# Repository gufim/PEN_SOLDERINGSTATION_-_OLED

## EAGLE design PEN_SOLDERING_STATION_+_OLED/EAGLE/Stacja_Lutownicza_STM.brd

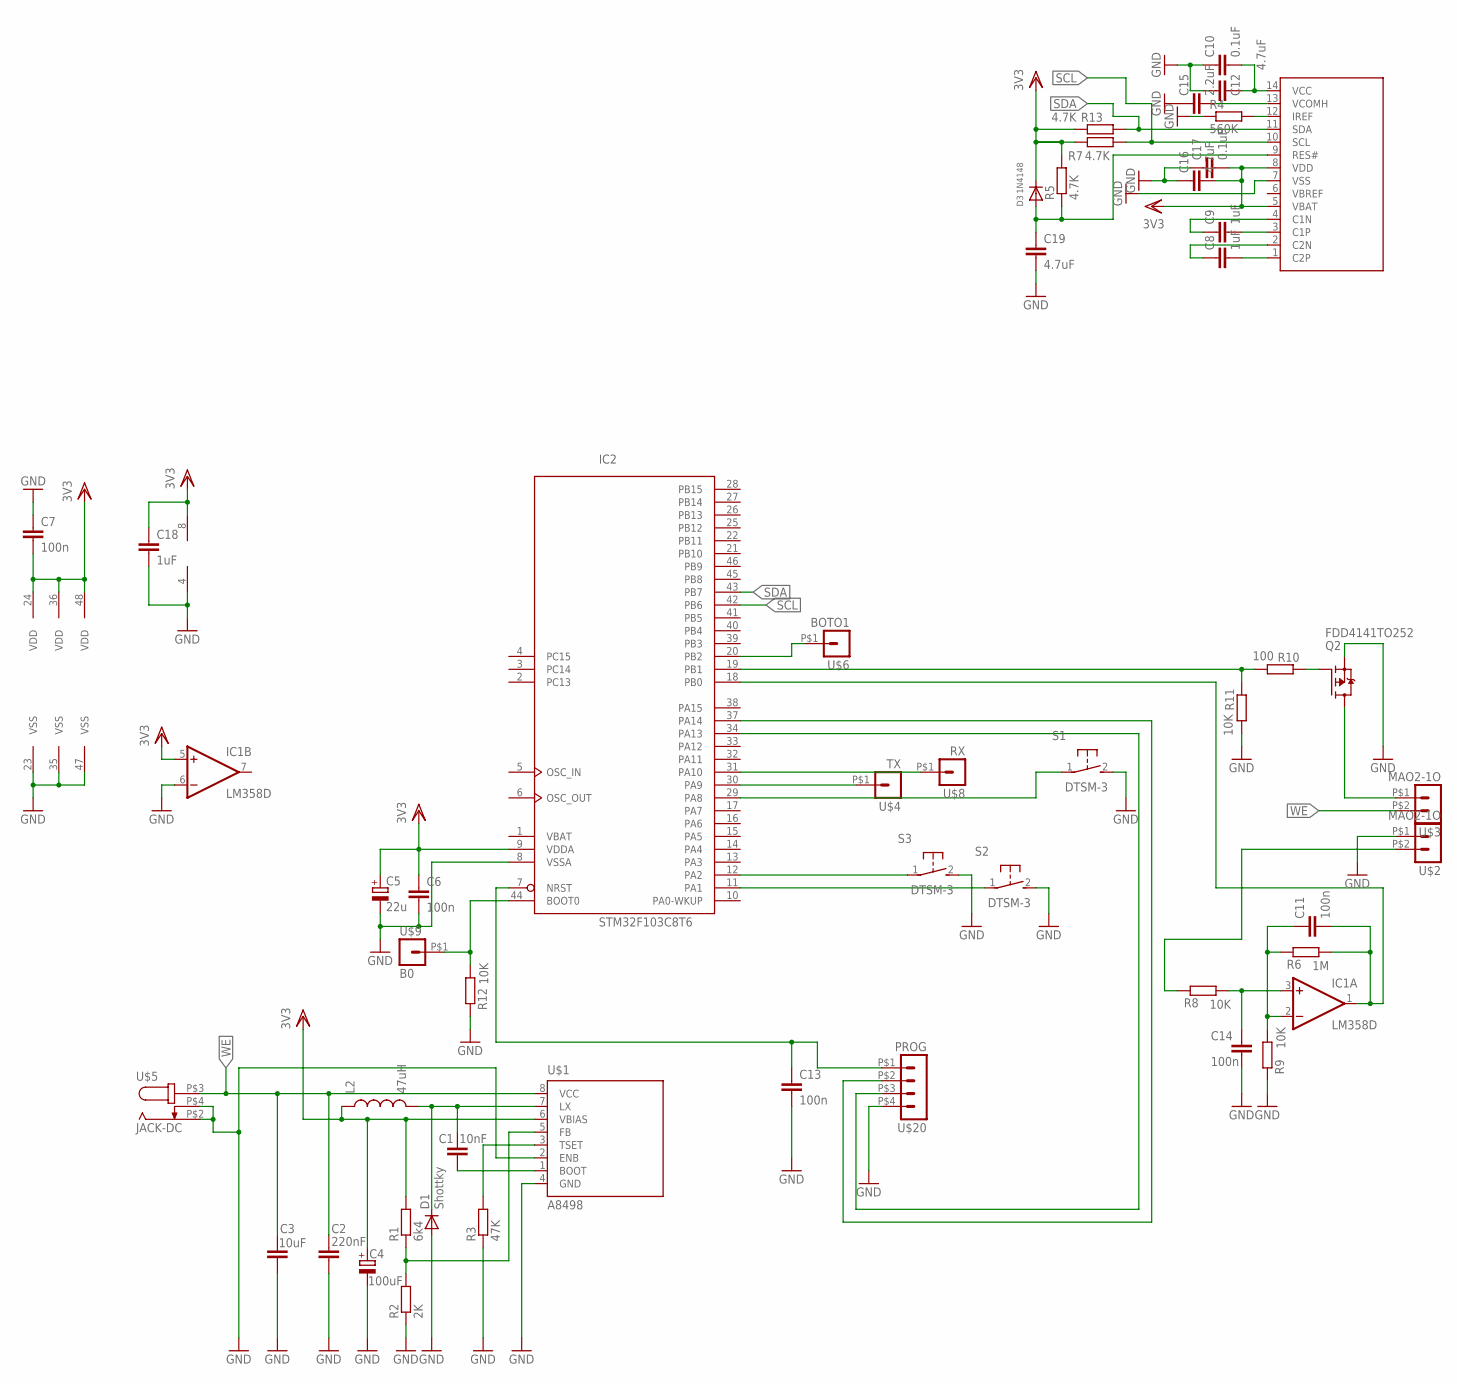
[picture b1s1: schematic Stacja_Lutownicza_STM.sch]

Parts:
C1: 10nF; C1206
C2: 220nF; C1210
C3: 10uF; C0603
C4: 100uF; SMC_D
C5: 22u; R/2012-12R
C6, C7, C11, C13, C14: 100n; C0603
C8, C9, C18: 1uF; C0603
C10, C17: 0.1uF; C0603
C12, C16, C19: 4.7uF; C0603
C15: 2.2uF; C0603
D1: Shottky; SOD-123_MINI-SMA
D3: 1N4148; SOD-323F
IC1: LM358D; SO08
IC2: STM32F103C8T6; LQFP48
L2: 47uH; INDUCTOR-1206
Q2: FDD4141TO252; TO252
R1: 6k4; R0603
R2: 2K; R0603
R3: 47K; R0603
R4: 560K; R0603
R5, R7, R13: 4.7K; R0603
R6: 1M; R0603
R8, R9, R11, R12: 10K; R0603
R10: 100; R0603
S1, S2, S3: DTSM-3
U$1: A8498; SO08
U$2, U$3: MAO2-1O
U$4: TX; MAO1-1O
U$5: JACK-DC
U$6: BOTO1; MAO1-1O
U$7: OLED_0_91
U$8: RX; MAO1-1O
U$9: B0; MAO1-1O
U$20: PROG; MAO4-4O

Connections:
GND: C2.2, C3.2, C4.-, C5.-, C6.2, C7.1, C10.1, C12.1, C13.2, C14.2, C15.1, C16.1, C17.1, C18.2, C19.2, D1.A, IC1.4 (V-), IC1.6 (-IN), IC2.8 (VSSA), IC2.23 (VSS), IC2.35 (VSS), IC2.47 (VSS), Q2.2 (S), R2.1, R3.1, R4.1, R9.1, R11.2, R12.1, S1.2, S2.2, S3.2, U$1.2 (ENB), U$1.4 (GND), U$2.P$1 (1), U$5.P$2 (1), U$5.P$4 (2), U$7.7 (VSS), U$20.P$4 (4)
unnamed: C1.2, D1.C, L2.P$2 (2), U$1.7 (LX)
unnamed: IC2.12 (PA2), S3.1
unnamed: IC2.29 (PA8), S1.1
unnamed: C1.1, U$1.1 (BOOT)
unnamed: IC2.30 (PA9), U$4.P$1
unnamed: R3.2, U$1.3 (TSET)
unnamed: R1.1, R2.2, U$1.5 (FB)
unnamed: IC2.31 (PA10), U$8.P$1
unnamed: IC2.11 (PA1), S2.1
unnamed: C11.2, IC1.1 (OUT), IC2.18 (PB0), R6.2
unnamed: IC2.44 (BOOT0), R12.2, U$9.P$1
unnamed: C11.1, IC1.2 (-IN), R6.1, R9.2
unnamed: C14.1, IC1.3 (+IN), R8.2
unnamed: IC2.20 (PB2), U$6.P$1
unnamed: C8.2, U$7.1 (C2P)
unnamed: C8.1, U$7.2 (C2N)
unnamed: C9.2, U$7.3 (C1P)
unnamed: C9.1, U$7.4 (C1N)
unnamed: IC2.37 (PA14), U$20.P$2 (2)
unnamed: IC2.34 (PA13), U$20.P$3 (3)
unnamed: C10.2, C12.2, U$7.14 (VCC)
unnamed: Q2.1 (G), R10.1
unnamed: R8.1, U$2.P$2 (2)
unnamed: IC2.19 (PB1), R10.2, R11.1
unnamed: Q2.3 (D), U$3.P$1 (1)
unnamed: C15.2, U$7.13 (VCOMH)
unnamed: R4.2, U$7.12 (IREF)
unnamed: C19.1, D3.A, R5.1, U$7.9 (RES#)
NRST: C13.1, IC2.7 (NRST), U$20.P$1 (1)
SCL: IC2.42 (PB6), R7.2, U$7.10 (SCL)
SDA: IC2.43 (PB7), R13.2, U$7.11 (SDA)
VBAT: IC2.1 (VBAT)
VDD: C4.+, C5.+, C6.1, C7.2, C16.2, C17.2, C18.1, D3.C, IC1.5 (+IN), IC1.8 (V+), IC2.9 (VDDA), IC2.24 (VDD), IC2.36 (VDD), IC2.48 (VDD), L2.P$1 (1), R1.2, R5.2, R7.1, R13.1, U$1.6 (VBIAS), U$7.5 (VBAT), U$7.8 (VDD)
WE: C2.1, C3.1, U$1.8 (VCC), U$3.P$2 (2), U$5.P$3 (3)

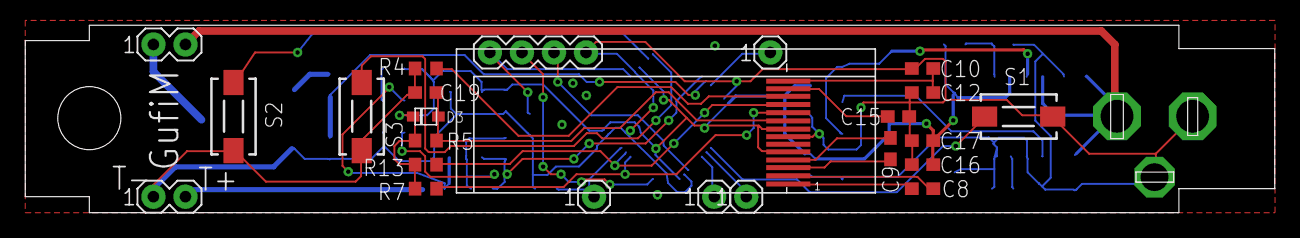
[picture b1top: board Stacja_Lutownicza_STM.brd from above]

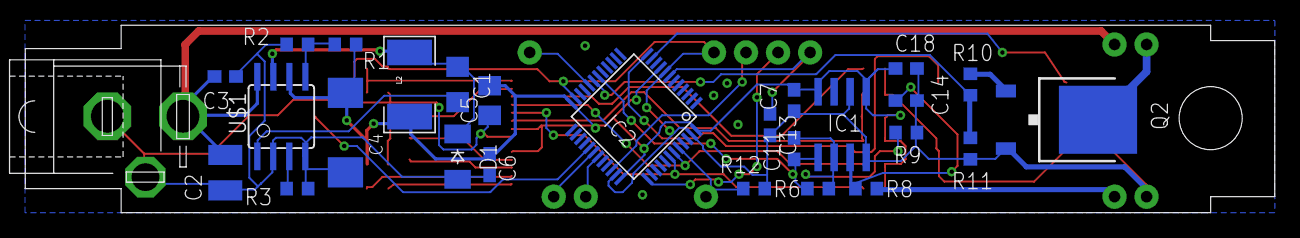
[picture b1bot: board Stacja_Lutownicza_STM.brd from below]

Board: 2 copper layers, 99.0 x 14.9 mm, 51 parts (27 on the bottom side), 34 nets.

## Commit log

2020-05-22 Created

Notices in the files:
parts and their libraries:
SparkFun: Licensing: CC v3.0 Share-Alike You are welcome to use this library for commercial purposes.
